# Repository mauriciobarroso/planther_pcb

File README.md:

# planther_pcb
PlanTher Project PCB

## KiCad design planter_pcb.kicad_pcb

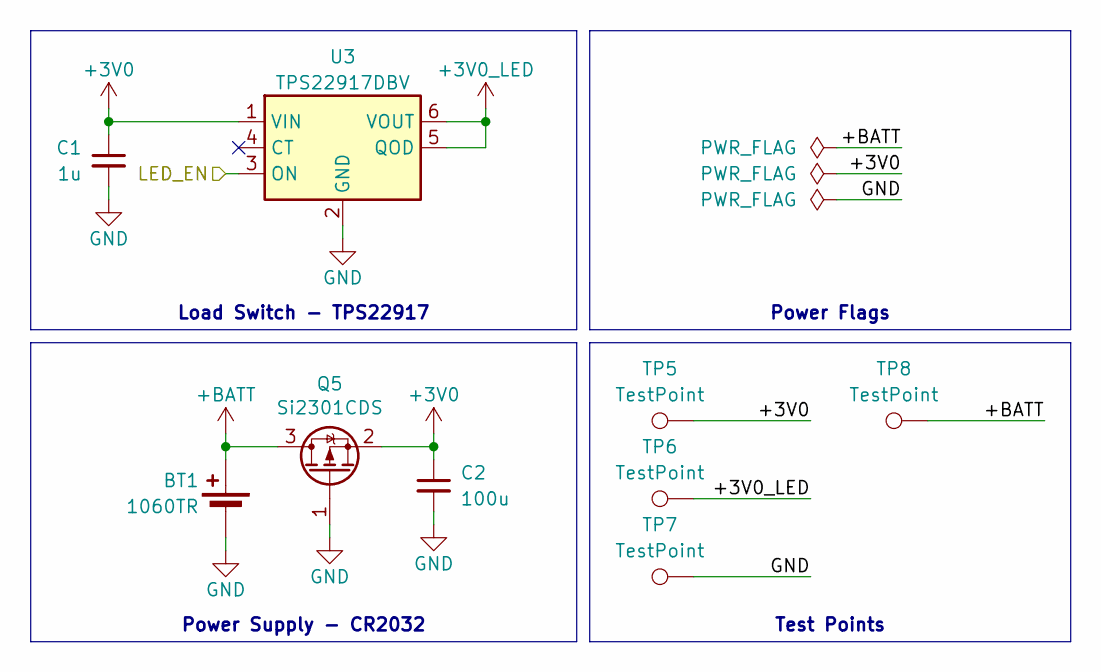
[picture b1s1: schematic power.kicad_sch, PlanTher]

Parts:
BT1: 1060TR; BatteryHolder_Keystone_1060_1x2032; LCSC C238069
C1: 1u; C_0603_1608Metric; LCSC C15849
C2: 100u; C_1206_3216Metric; LCSC C15008
Q5: Si2301CDS; SOT-23; LCSC C10487
TP5, TP6, TP7, TP8: TestPoint; TestPoint_Pad_D1.0mm
U3: TPS22917DBV; SOT-23-6; LCSC C2681320

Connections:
+3V0: C1.1, C2.1, Q5.2 (S), TP5.1, U3.1 (VIN); also elsewhere on the board
+3V0_LED: TP6.1, U3.5 (QOD), U3.6 (VOUT); also elsewhere on the board
+BATT: BT1.1 (+), Q5.3 (D), TP8.1
/MCU/LED_EN: U3.3 (ON); also elsewhere on the board
GND: BT1.2 (-), C1.2, C2.2, Q5.1 (G), TP7.1, U3.2 (GND); also elsewhere on the board

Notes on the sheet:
Power Flags
Power Supply - CR2032
Test Points
Load Switch - TPS22917

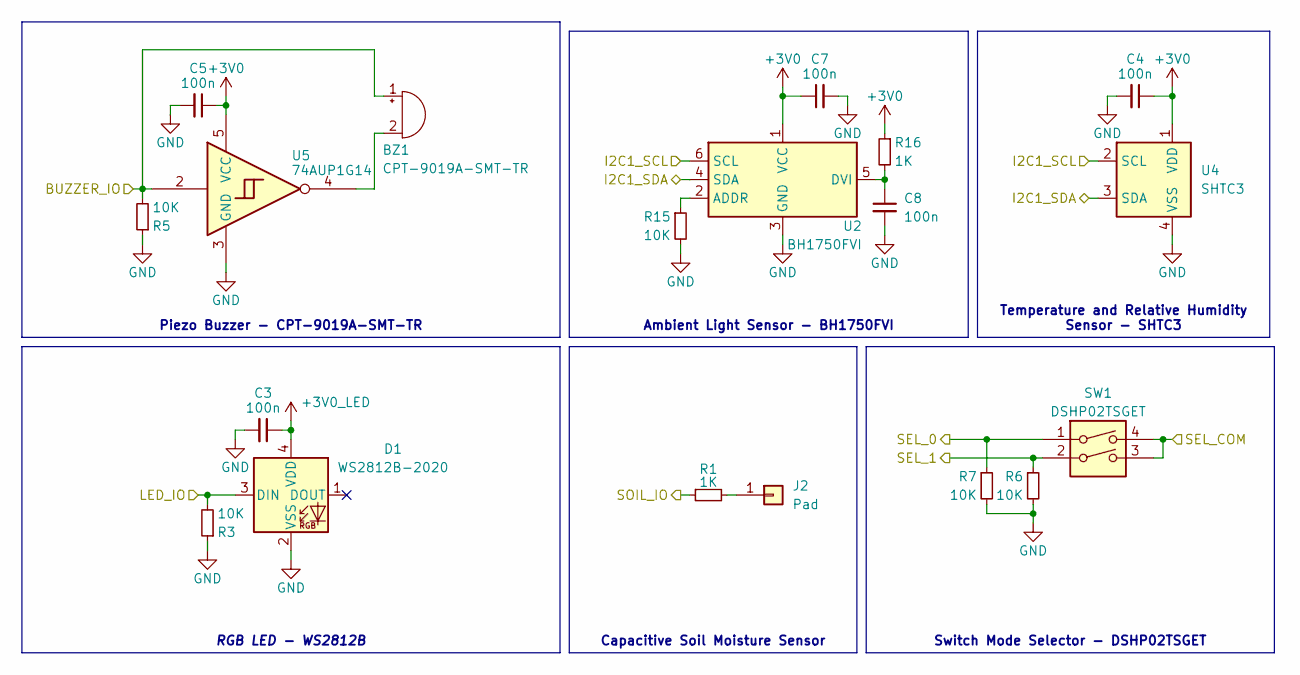
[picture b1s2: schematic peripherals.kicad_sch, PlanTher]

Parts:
BZ1: CPT-9019A-SMT-TR; Buzzer_CUI_CPT-9019S-SMT; LCSC C20181991
C3, C4, C5, C7, C8: 100n; C_0603_1608Metric; LCSC C14663
D1: WS2812B-2020; LED_WS2812B-2020_PLCC4_2.0x2.0mm; LCSC C965555
J2: Pad; SoilMoisture_Pad
R1, R16: 1K; R_0603_1608Metric; LCSC C21190
R3, R5, R6, R7, R15: 10K; R_0603_1608Metric; LCSC C25804
SW1: DSHP02TSGET; SW_DIP_SPSTx02_Slide_KingTek_DSHP02TS_W7.62mm_P1.27mm; LCSC C40735
U2: BH1750FVI; LCSC C78960
U4: SHTC3; Sensirion_DFN-4-1EP_2x2mm_P1mm_EP0.7x1.6mm; LCSC C2880044
U5: 74AUP1G14; SOT-23-5; LCSC C2682131

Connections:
+3V0: C4.1, C5.1, C7.1, R16.1, U2.1 (VCC), U4.1 (VDD), U5.5 (VCC); also elsewhere on the board
+3V0_LED: C3.1, D1.4 (VDD); also elsewhere on the board
/MCU/BUZZER_IO: BZ1.1 (+), R5.2, U5.2; also elsewhere on the board
/MCU/I2C1_SCL: U2.6 (SCL), U4.2 (SCL); also elsewhere on the board
/MCU/I2C1_SDA: U2.4 (SDA), U4.3 (SDA); also elsewhere on the board
/MCU/LED_IO: D1.3 (DIN), R3.2; also elsewhere on the board
/MCU/SEL_0: R7.1, SW1.1; also elsewhere on the board
/MCU/SEL_1: R6.1, SW1.2; also elsewhere on the board
/MCU/SEL_COM: SW1.3, SW1.4; also elsewhere on the board
/MCU/SOIL_IO: R1.1; also elsewhere on the board
GND: C3.2, C4.2, C5.2, C7.2, C8.2, D1.2 (VSS), R3.1, R5.1, R6.2, R7.2, R15.2, U2.3 (GND), U4.4 (VSS), U5.3 (GND); also elsewhere on the board
unnamed: BZ1.2 (-), U5.4
unnamed: J2.1, R1.2
unnamed: R15.1, U2.2 (ADDR)
unnamed: C8.1, R16.2, U2.5 (DVI)

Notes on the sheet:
RGB LED - WS2812B
Ambient Light Sensor - BH1750FVI
Temperature and Relative Humidity Sensor - SHTC3
Piezo Buzzer - CPT-9019A-SMT-TR
Switch Mode Selector - DSHP02TSGET
Capacitive Soil Moisture Sensor

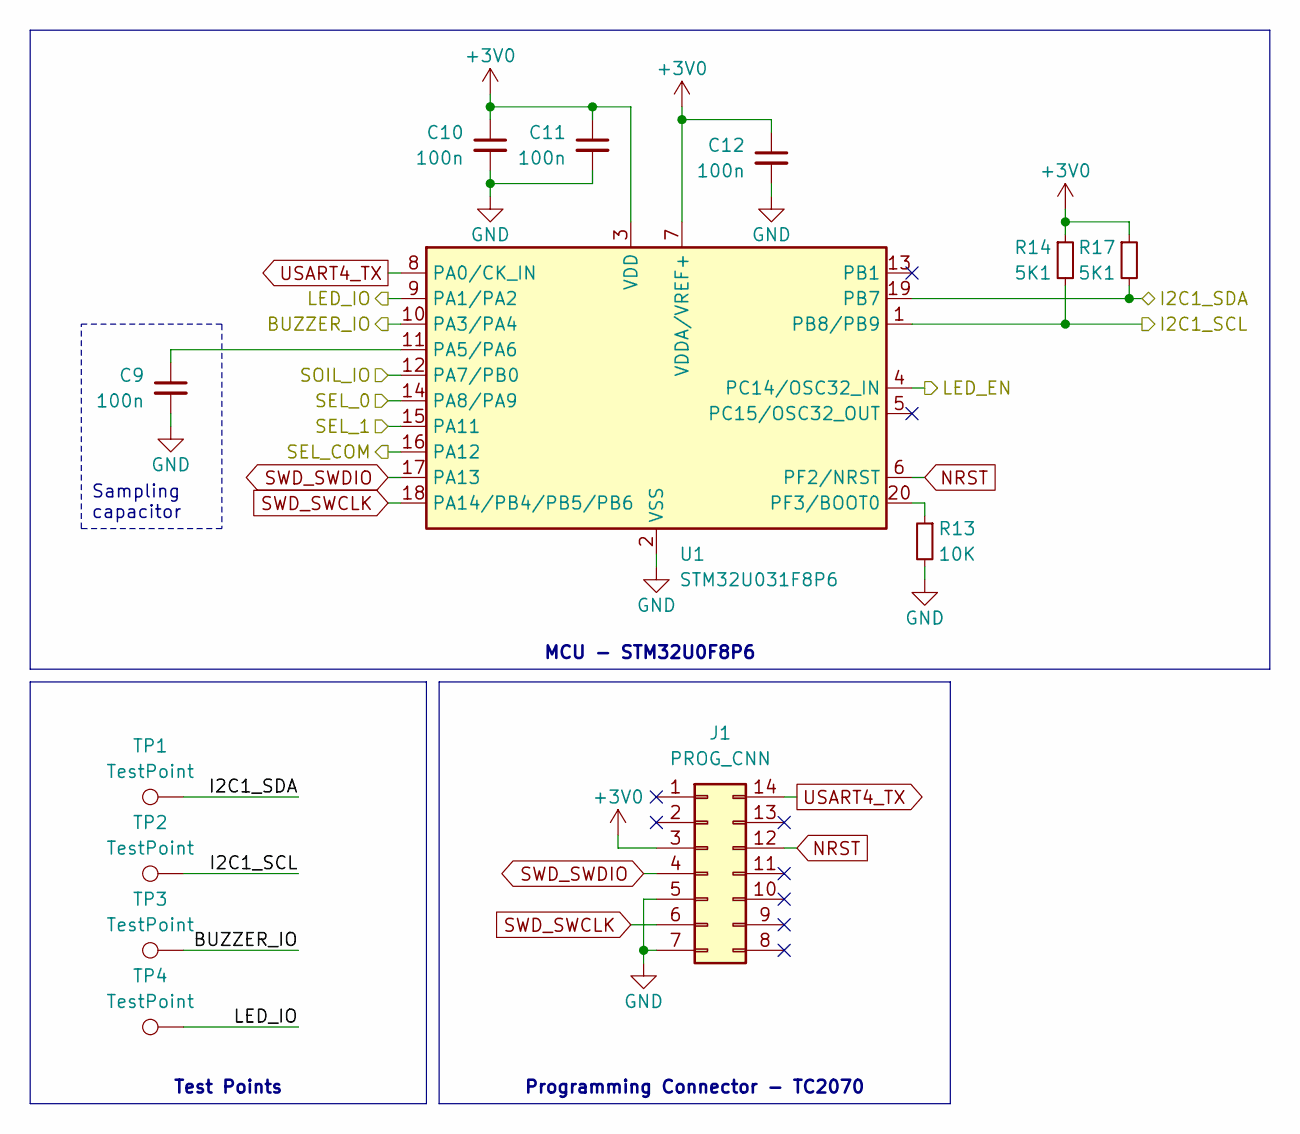
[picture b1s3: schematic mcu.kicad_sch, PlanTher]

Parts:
C9, C10, C11, C12: 100n; C_0603_1608Metric; LCSC C14663
J1: PROG_CNN; Tag-Connect_TC2070-IDC-FP_2x07_P1.27mm_Vertical
R13: 10K; R_0603_1608Metric; LCSC C25804
R14, R17: 5K1; R_0603_1608Metric; LCSC C23186
TP1, TP2, TP3, TP4: TestPoint; TestPoint_Pad_D1.0mm
U1: STM32U031F8P6; TSSOP-20_4.4x6.5mm_P0.65mm; LCSC C22808553

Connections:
+3V0: C10.1, C11.1, C12.1, J1.3, R14.1, R17.1, U1.3 (VDD), U1.7 (VDDA/VREF+); also elsewhere on the board
/MCU/BUZZER_IO: TP3.1, U1.10 (PA3/PA4); also elsewhere on the board
/MCU/I2C1_SCL: R14.2, TP2.1, U1.1 (PB8/PB9); also elsewhere on the board
/MCU/I2C1_SDA: R17.2, TP1.1, U1.19 (PB7); also elsewhere on the board
/MCU/LED_EN: U1.4 (PC14/OSC32_IN); also elsewhere on the board
/MCU/LED_IO: TP4.1, U1.9 (PA1/PA2); also elsewhere on the board
/MCU/SEL_0: U1.14 (PA8/PA9); also elsewhere on the board
/MCU/SEL_1: U1.15 (PA11); also elsewhere on the board
/MCU/SEL_COM: U1.16 (PA12); also elsewhere on the board
/MCU/SOIL_IO: U1.12 (PA7/PB0); also elsewhere on the board
GND: C9.2, C10.2, C11.2, C12.2, J1.5, J1.7, R13.2, U1.2 (VSS); also elsewhere on the board
NRST: J1.12, U1.6 (PF2/NRST)
unnamed: C9.1, U1.11 (PA5/PA6)
unnamed: R13.1, U1.20 (PF3/BOOT0)
SWD_SWCLK: J1.6, U1.18 (PA14/PB4/PB5/PB6)
SWD_SWDIO: J1.4, U1.17 (PA13)
USART4_TX: J1.14, U1.8 (PA0/CK_IN)

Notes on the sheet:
MCU - STM32U0F8P6
Test Points
Programming Connector - TC2070
Sampling capacitor

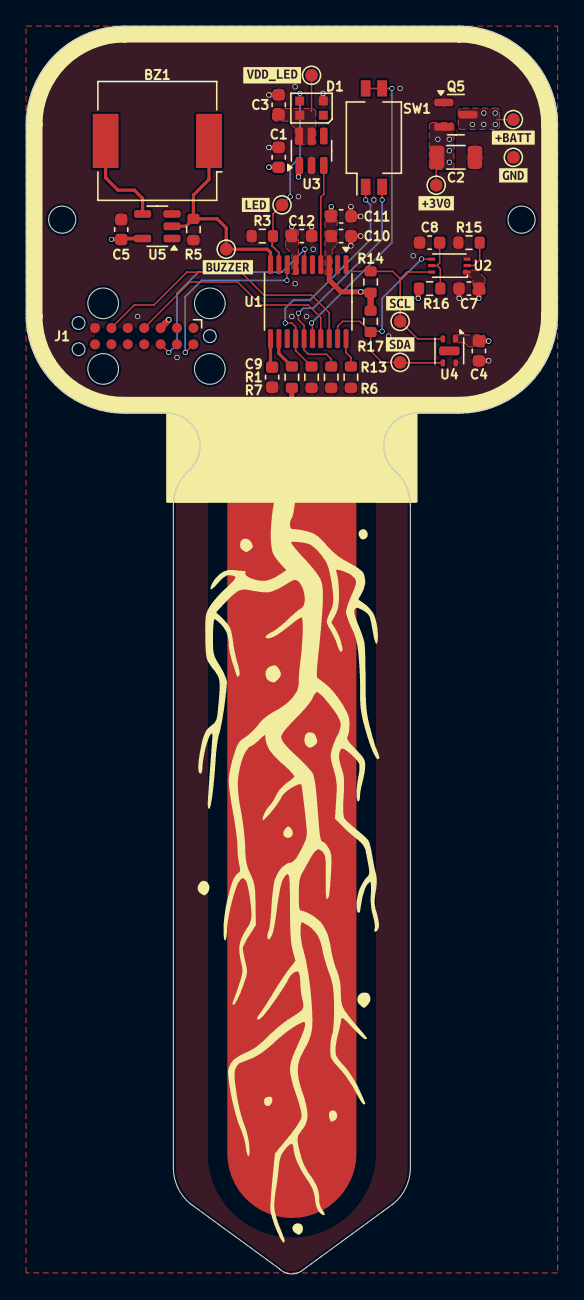
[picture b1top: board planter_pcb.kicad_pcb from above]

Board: 4 copper layers, 41.1 x 96.6 mm, 49 parts (1 on the bottom side), 23 nets.

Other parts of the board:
kibuzzard-6805202F: G***; kibuzzard-6805202F
kibuzzard-6805203A: G***; kibuzzard-6805203A
kibuzzard-6805205E: G***; kibuzzard-6805205E
kibuzzard-68052017: G***; kibuzzard-68052017
kibuzzard-68052025: G***; kibuzzard-68052025
kibuzzard-68052045: G***; kibuzzard-68052045
kibuzzard-68052051: G***; kibuzzard-68052051
kibuzzard-68052059: G***; kibuzzard-68052059

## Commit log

2025-04-23 added .gitignore
2025-04-23 added schematics
2025-04-23 added main schematic
2025-04-23 added pcb layout
2025-04-23 updated .gitignore to ignore json files
2025-04-23 added kicad project file
2026-05-15 updated last changes
